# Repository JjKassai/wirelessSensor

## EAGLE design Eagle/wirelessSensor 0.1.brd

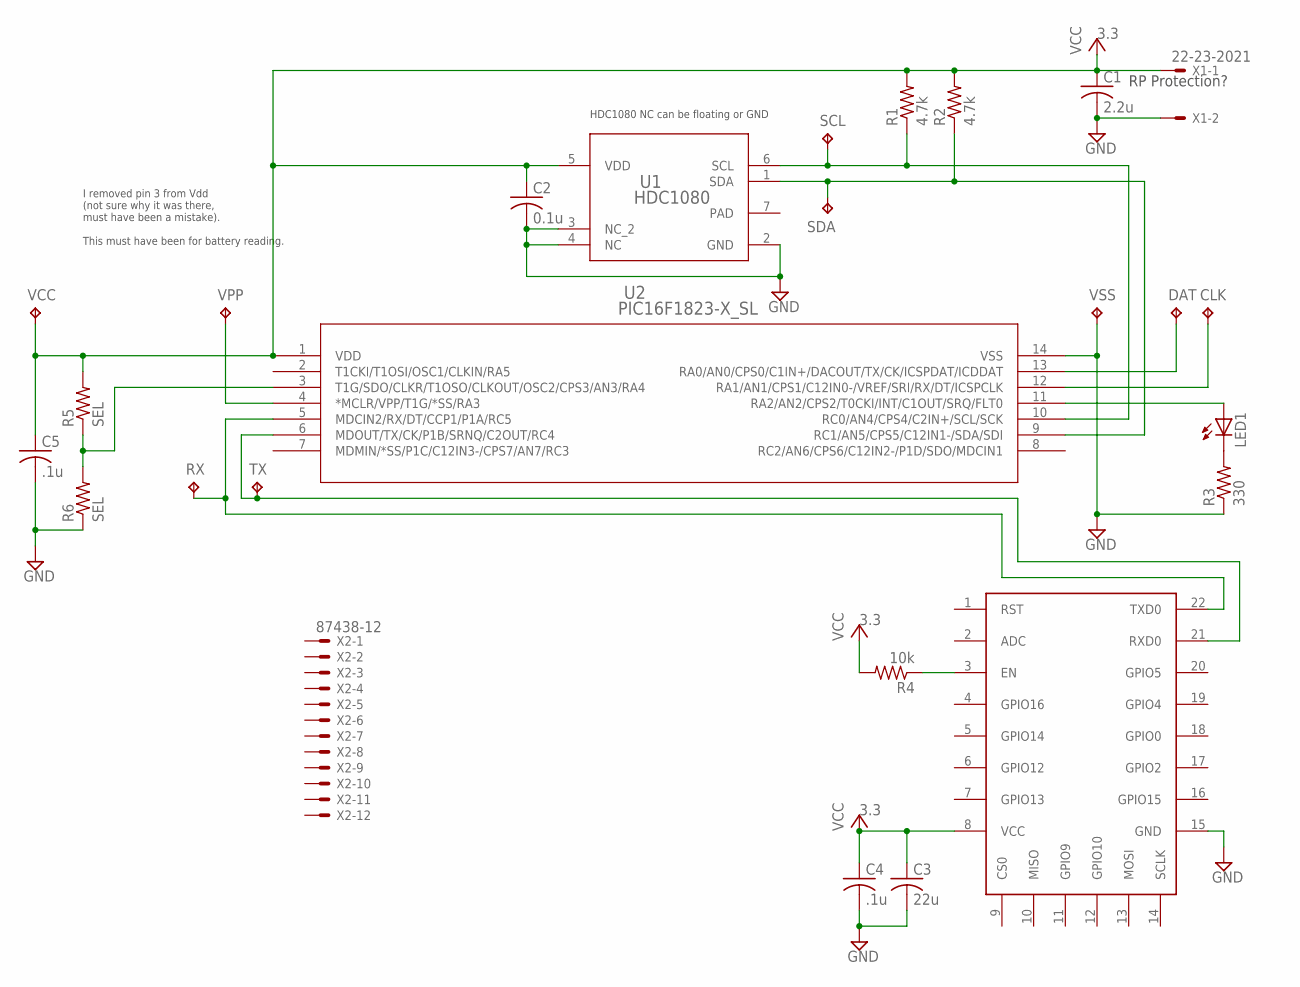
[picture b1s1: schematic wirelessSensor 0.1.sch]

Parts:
C1: 2.2u; C0603
C2: 0.1u; C0603
C3: 22u; C0603K
C4, C5: .1u; C0603K
CLK: TPB1,27; B1,27
DAT: TPB1,27; B1,27
LED1: LEDCHIP-LED0603; CHIP-LED0603
R1, R2: 4.7k; R0603
R3: 330; R0603
R4: 10k; R0603
R5, R6: SEL; R0603
RX: TPB1,27; B1,27
SCL: TPB1,27; B1,27
SDA: TPB1,27; B1,27
TX: TPB1,27; B1,27
U1: HDC1080; DMB0006A
U2: PIC16F1823-X_SL; SOIC14-N_MC
U$1: ESP8266-12E
VCC: TPB1,27; B1,27
VPP: TPB1,27; B1,27
VSS: TPB1,27; B1,27
X1: 22-23-2021
X2: 87438-12

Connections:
GND: C1.2, C2.2, C3.2, C4.2, C5.2, R3.1, R6.1, U1.2 (GND), U1.3 (NC_2), U1.4 (NC), U2.14 (VSS), U$1.15 (GND), VSS.TP, X1.2
unnamed: RX.TP, U2.5 (MDCIN2/RX/DT/CCP1/P1A/RC5), U$1.22 (TXD0)
unnamed: R1.1, SCL.TP, U1.6 (SCL), U2.10 (RC0/AN4/CPS4/C2IN+/SCL/SCK)
unnamed: R2.1, SDA.TP, U1.1 (SDA), U2.9 (RC1/AN5/CPS5/C12IN1-/SDA/SDI)
unnamed: U2.4 (*MCLR/VPP/T1G/*SS/RA3), VPP.TP
unnamed: DAT.TP, U2.13 (RA0/AN0/CPS0/C1IN+/DACOUT/TX/CK/ICSPDAT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)
unnamed: CLK.TP, U2.12 (RA1/AN1/CPS1/C12IN0-/VREF/SRI/RX/DT/ICS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)
unnamed: R4.1, U$1.3 (EN)
unnamed: TX.TP, U2.6 (MDOUT/TX/CK/P1B/SRNQ/C2OUT/RC4), U$1.21 (RXD0)
unnamed: R5.1, R6.2, U2.3 (T1G/SDO/CLKR/T1OSO/CLKOUT/OSC2/CPS3/AN3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)
unnamed: LED1.A, U2.11 (RA2/AN2/CPS2/T0CKI/INT/C1OUT/SRQ/FLT0)
unnamed: LED1.C, R3.2
PAD: U1.7 (PAD)
VCC: C1.1, C2.1, C3.1, C4.1, C5.1, R1.2, R2.2, R4.2, R5.2, U1.5 (VDD), U2.1 (VDD), U$1.8 (VCC), VCC.TP, X1.1

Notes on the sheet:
I removed pin 3 from Vdd (not sure why it was there, must have been a mistake). This must have been for battery reading.
HDC1080 NC can be floating or GND
RP Protection?

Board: 2 copper layers, 26 parts (16 on the bottom side), 13 nets, no tracks yet.

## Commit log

2016-11-15 Added datasheets for basic components
2016-11-16 Started a library of the necessary components and a basic schematic using the PIC16F1823 (phsyically smaller part)
2016-11-18 Started an Eagle layout and schematic
2016-11-22 Started a battery life calculation spreadsheet
2016-11-23 Looked further into battery possibilities, added some additional datasheets
2016-11-29 Added some information on low-cost, low-power radios, and organized the root folder
2016-12-01 Started the MPLAB project and added some skeleton source files
2016-12-01 More from previous check-in I forgot to include
2016-12-02 Added some new information about the specific ESP8266 module I have (ESP-12-E)
2016-12-02 Updated the MPLAB project with some basic initialization code
2016-12-06 Finished up basic setup for UART - should be able to test basic communication now
2016-12-07 Started work on the I2C interface, and organized the code a bit more
2016-12-08 Started some functions for the ESP8266 module
2016-12-09 Added some diagnostics, got the UART working without problems. Still working on the I2C.
2016-12-09 Started I2C files and tried to clean up the code; added some information about I2C bus
2016-12-16 Migrated the project to the PIC16LF1825 and added the datasheet. Fixed i2c as well, I wasn't setting the ACKEN bit to start the acknowledge sequence after the first byte of data was recieved
2016-12-16 Quick clean-up!
2016-12-16 Added function to write HDC1080 configuration register, cleaned up a bit
2016-12-16 Removed spaces from directory names, started work on ESP8266 module
2016-12-16 Changed .gitignore to match the directory changes, started cleaning up the layout
2016-12-16 Updated the layout a bit, should be ready for review/close to ready for order
2016-12-19 Started laying out the board to include the ESP8266 given the Seeed studio board deal (100mm dimensions)
2016-12-20 Started working on the ESP8266, having some trouble with buffer overrun on the PIC. Started some board layout
2016-12-20 Wrapping up the schematic before board order; minor firmware adjustments; added CAM file for Gerber generation
2016-12-21 Finalized a working firmware that reports relevant information automatically when connecting.
2016-12-21 More work on the PCB, added some SeeedStudio specific files (cam generator, DRC rules)
